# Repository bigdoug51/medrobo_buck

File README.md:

just some med robo stuff. this is a buck that converts 7.4v to 4.5v

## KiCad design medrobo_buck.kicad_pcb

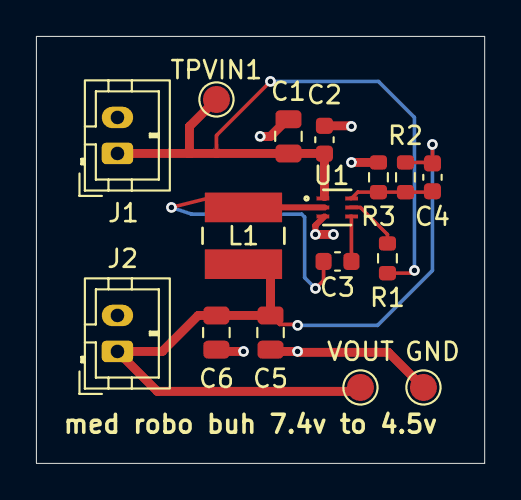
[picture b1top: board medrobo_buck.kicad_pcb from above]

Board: 4 copper layers, 24.9 x 23.7 mm, 16 parts (0 on the bottom side), 7 nets.

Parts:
C1: 10uF; C_0805_2012Metric
C2, C3: 100nF; C_0603_1608Metric
C4: 18pF; C_0603_1608Metric
C5, C6: 22uF; C_0805_2012Metric
GND: TestPoint; TestPoint_Pad_D1.5mm
J1: battery in; JST_PH_B2B-PH-K_1x02_P2.00mm_Vertical
J2: output; JST_PH_B2B-PH-K_1x02_P2.00mm_Vertical
L1: 4.7uH; IND_4532-WE-PD2_WRE
R1: 100k; R_0603_1608Metric
R2: 195k; R_0603_1608Metric
R3: 30k; R_0603_1608Metric
TPVIN1: TestPoint; TestPoint_Pad_D1.5mm
U1: TPS563203; SOT-5X3-6_DRL_TEX
VOUT: TestPoint; TestPoint_Pad_D1.5mm

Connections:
/BST: C3.1, U1.4 (BST)
/EN: R1.2, U1.5 (EN)
/FB: C4.2, R2.2, R3.1, U1.6 (FB)
/SW: C3.2, L1.1, U1.2 (SW)
/VIN: C1.1, C2.1, J1.1, R1.1, TPVIN1.1 (1_1), U1.1 (VIN)
/VOUT: C4.1, C5.1, C6.1, J2.1, L1.2, R2.1, VOUT.1 (1_1)
GND: C1.2, C2.2, C5.2, C6.2, GND.1 (1_1), J1.2, J2.2, R3.2, U1.3 (GND)
